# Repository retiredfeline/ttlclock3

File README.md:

# TTL ternary clock

These are the KiCad design files for my Hackaday project [TTL ternary clock](https://hackaday.io/project/183765-ttl-ternary-clock).

Simulations of the 74LS74 based flip-flop-flap and built-up counters are in falstad and logisim directories.

## Versioning

First release January 2022

## Authors

* **Ken Yap**

## License

See the [LICENSE](LICENSE.md) file for license rights and limitations (MIT).

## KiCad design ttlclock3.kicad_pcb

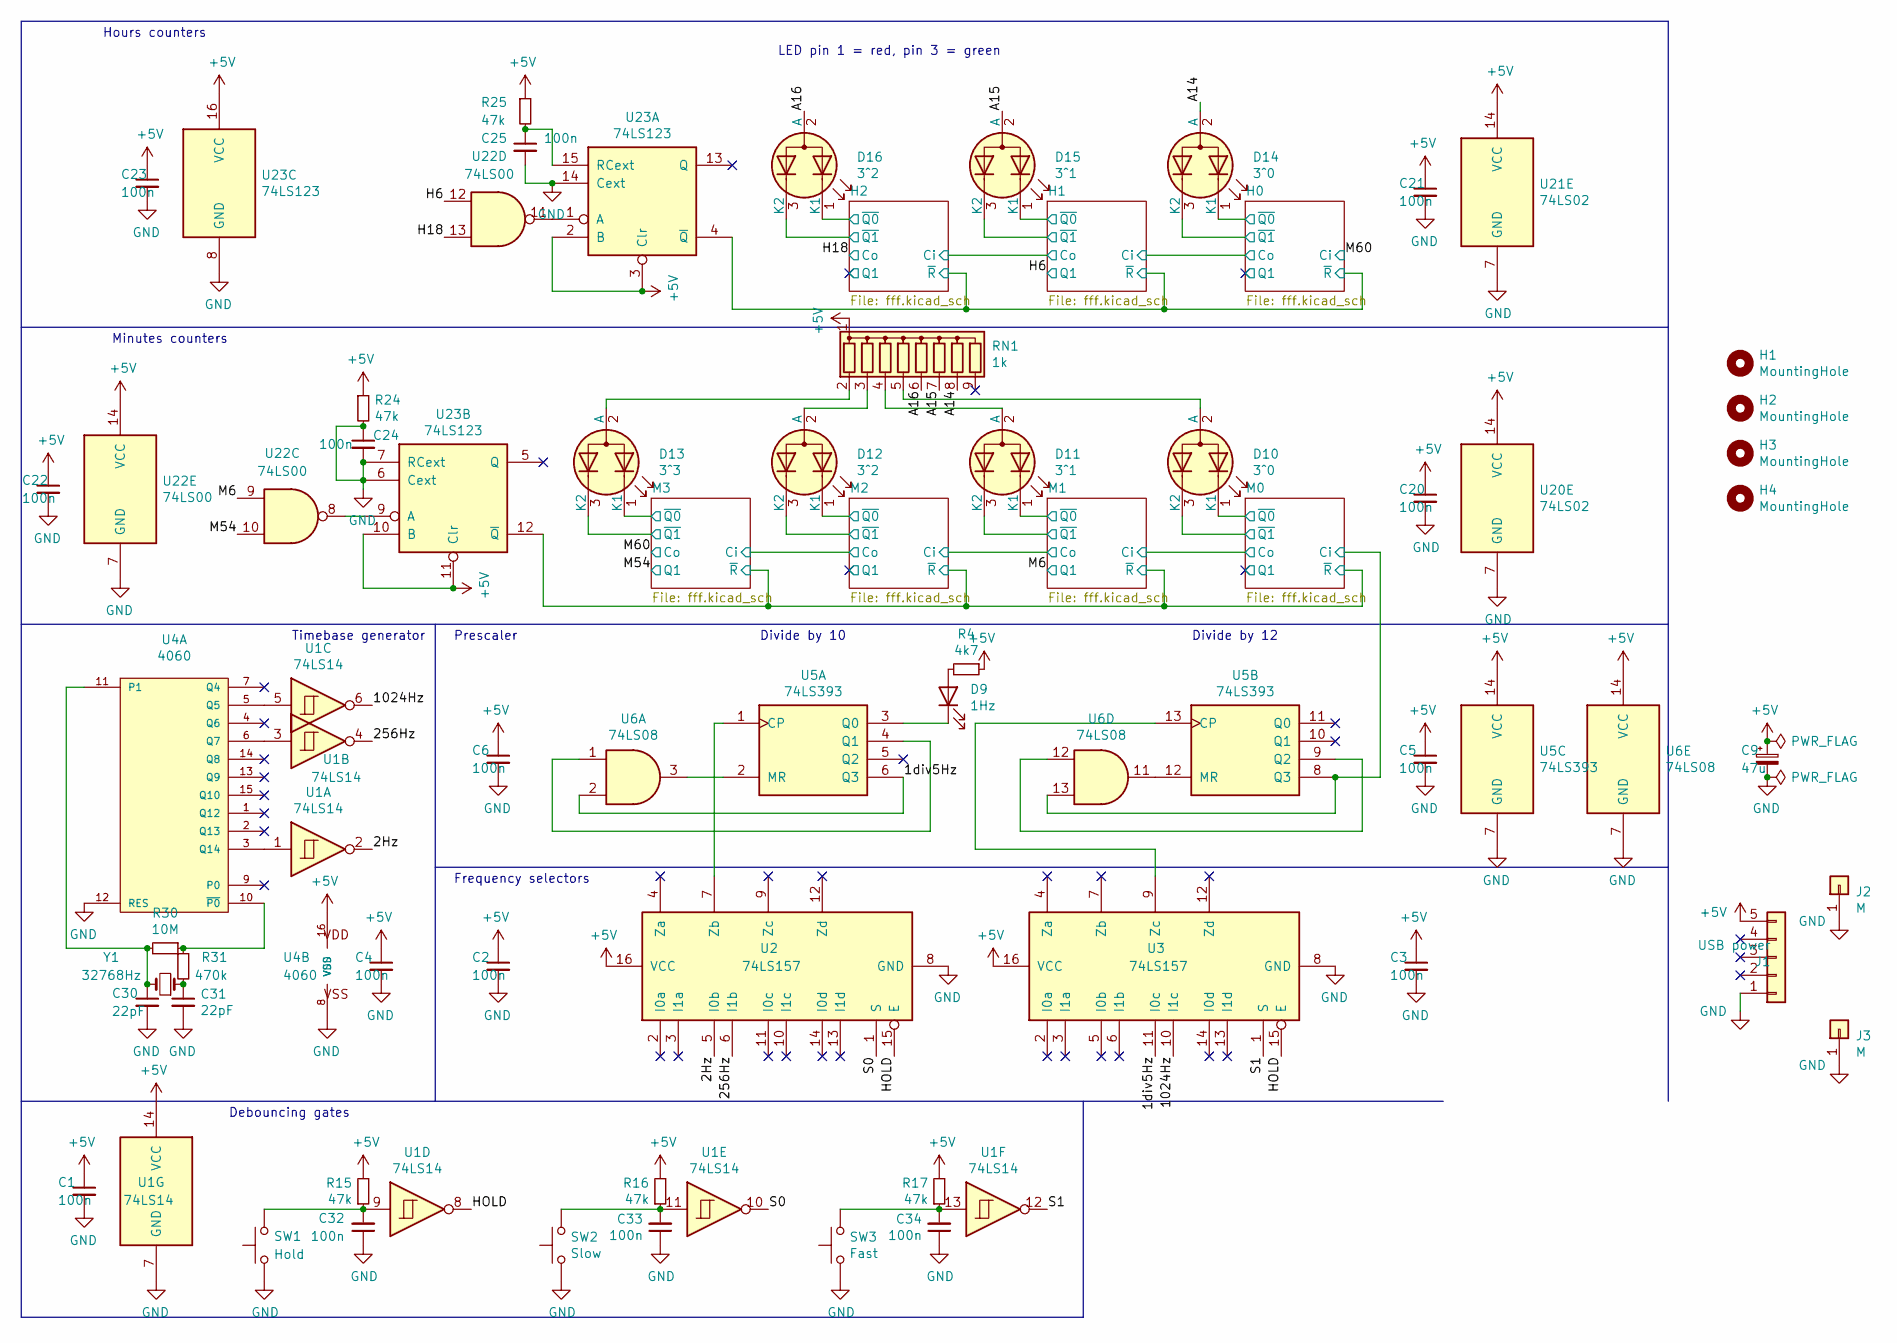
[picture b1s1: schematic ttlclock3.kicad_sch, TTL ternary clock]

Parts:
C1, C2, C3, C4, C5, C6, C20, C21, C22, C23: 100n; C_Rect_L7.2mm_W2.5mm_P5.00mm_FKS2_FKP2_MKS2_MKP2
C9: 47u; CP_Radial_D6.3mm_P2.50mm
C24, C25, C32, C33, C34: 100n; C_Disc_D3.4mm_W2.1mm_P2.50mm
C30, C31: 22pF; C_Disc_D3.0mm_W1.6mm_P2.50mm
D9: 1Hz; LED_D3.0mm
D10, D14: 3^0; LED_D5.0mm-3
D11, D15: 3^1; LED_D5.0mm-3
D12, D16: 3^2; LED_D5.0mm-3
D13: 3^3; LED_D5.0mm-3
H1, H2, H3, H4: MountingHole; MountingHole_3.5mm_Pad
J1: USB power; PinHeader_1x05_P2.54mm_Vertical
J2, J3: M; PinHeader_1x01_P2.54mm_Vertical
R4: 4k7; R_Axial_DIN0207_L6.3mm_D2.5mm_P10.16mm_Horizontal
R15, R16, R17, R24, R25: 47k; R_Axial_DIN0207_L6.3mm_D2.5mm_P10.16mm_Horizontal
R30: 10M; R_Axial_DIN0207_L6.3mm_D2.5mm_P10.16mm_Horizontal
R31: 470k; R_Axial_DIN0207_L6.3mm_D2.5mm_P10.16mm_Horizontal
RN1: 1k; R_Array_SIP9
SW1: Hold; SW_PUSH_6mm_H4.3mm
SW2: Slow; SW_PUSH_6mm_H4.3mm
SW3: Fast; SW_PUSH_6mm_H4.3mm
U1: 74LS14; DIP-14_W7.62mm
U2, U3: 74LS157; DIP-16_W7.62mm
U4: 4060; DIP-16_W7.62mm
U5: 74LS393; DIP-14_W7.62mm
U6: 74LS08; DIP-14_W7.62mm
U20, U21: 74LS02; DIP-14_W7.62mm
U22: 74LS00; DIP-14_W7.62mm
U23: 74LS123; DIP-16_W7.62mm
Y1: 32768Hz; Crystal_C38-LF_D3.0mm_L8.0mm_Horizontal

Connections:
+5V: C1.1, C2.1, C3.1, C4.1, C5.1, C6.1, C9.1, C20.1, C21.1, C22.1, C23.1, J1.5, R4.1, R15.2, R16.2, R17.2, R24.1, R25.1, RN1.1 (common), U1.14 (VCC), U2.16 (VCC), U3.16 (VCC), U4.16 (VDD), U5.14 (VCC), U6.14 (VCC), U20.14 (VCC), U21.14 (VCC), U22.14 (VCC), U23.2 (B), U23.3 (Clr), U23.10 (B), U23.11 (Clr), U23.16 (VCC); also elsewhere on the board
/1div5Hz: U3.11 (I0c), U5.6 (Q3), U6.2
/2Hz: U1.2, U2.5 (I0b)
/256Hz: U1.4, U2.6 (I1b)
/1024Hz: U1.6, U3.10 (I1c)
/A14: D14.2 (A), RN1.8 (R7)
/A15: D15.2 (A), RN1.7 (R6)
/A16: D16.2 (A), RN1.6 (R5)
/H0/~Q0: D14.1 (K1); also elsewhere on the board
/H0/~Q1: D14.3 (K2); also elsewhere on the board
/H0/~R: U23.4 (~Q); also elsewhere on the board
/H1/Co: U21.10; also elsewhere on the board
/H1/~Q0: D15.1 (K1); also elsewhere on the board
/H1/~Q1: D15.3 (K2); also elsewhere on the board
/H2/Q1: U21.3; also elsewhere on the board
/H2/~Q0: D16.1 (K1); also elsewhere on the board
/H2/~Q1: D16.3 (K2); also elsewhere on the board
/H6: U21.9, U22.12; also elsewhere on the board
/H18: U21.1, U22.13; also elsewhere on the board
/HOLD: U1.8, U2.15 (E), U3.15 (E)
/M0/Ci: U5.8 (Q3), U6.13; also elsewhere on the board
/M0/Co: U20.10; also elsewhere on the board
/M0/Q1: U20.9; also elsewhere on the board
/M0/~Q0: D10.1 (K1); also elsewhere on the board
/M0/~Q1: D10.3 (K2); also elsewhere on the board
/M0/~R: U23.12 (~Q); also elsewhere on the board
/M1/~Q0: D11.1 (K1); also elsewhere on the board
/M1/~Q1: D11.3 (K2); also elsewhere on the board
/M2/Co: U20.1; also elsewhere on the board
/M2/Q1: U20.3; also elsewhere on the board
/M2/~Q0: D12.1 (K1); also elsewhere on the board
/M2/~Q1: D12.3 (K2); also elsewhere on the board
/M3/~Q0: D13.1 (K1); also elsewhere on the board
/M3/~Q1: D13.3 (K2); also elsewhere on the board
/M6: U22.9; also elsewhere on the board
/M54: U20.6, U22.10; also elsewhere on the board
/M60: U20.4; also elsewhere on the board
/S0: U1.10, U2.1 (S)
/S1: U1.12, U3.1 (S)
GND: C1.2, C2.2, C3.2, C4.2, C5.2, C6.2, C9.2, C20.2, C21.2, C22.2, C23.2, C24.1, C24.2, C25.2, C30.2, C31.2, C32.1, C33.1, C34.1, J1.1, J2.1, J3.1, R24.2, SW1.1, SW2.1, SW3.1, U1.7 (GND), U2.8 (GND), U3.8 (GND), U4.8 (VSS), U4.12 (RES), U5.7 (GND), U6.7 (GND), U20.7 (GND), U21.7 (GND), U22.7 (GND), U23.6 (Cext), U23.7 (RCext), U23.8 (GND), U23.14 (Cext); also elsewhere on the board
unnamed: C31.1, R31.2, Y1.1
unnamed: C32.2, R15.1, SW1.2, U1.9
unnamed: C33.2, R16.1, SW2.2, U1.11
unnamed: C34.2, R17.1, SW3.2, U1.13
unnamed: D9.2 (A), R4.2
unnamed: D9.1 (K), U5.3 (Q0)
unnamed: D10.2 (A), RN1.5 (R4)
unnamed: D11.2 (A), RN1.4 (R3)
unnamed: D12.2 (A), RN1.3 (R2)
unnamed: D13.2 (A), RN1.2 (R1)
unnamed: U2.7 (Zb), U5.1 (CP)
unnamed: U3.9 (Zc), U5.13 (CP)
unnamed: C30.1, R30.2, U4.11 (P1), Y1.2
unnamed: U1.5, U4.5 (Q5)
unnamed: U1.3, U4.6 (Q7)
unnamed: U1.1, U4.3 (Q14)
unnamed: R30.1, R31.1, U4.10 (~P0)
unnamed: U5.2 (MR), U6.3
unnamed: U5.4 (Q1), U6.1
unnamed: U5.12 (MR), U6.11
unnamed: U5.9 (Q2), U6.12
unnamed 64: U20.8; also elsewhere on the board
unnamed 66: U20.2; also elsewhere on the board
unnamed 67: U20.5; also elsewhere on the board
unnamed 69: U21.8; also elsewhere on the board
unnamed 70: U21.2; also elsewhere on the board
unnamed: U22.11, U23.1 (A)
unnamed: C25.1, R25.2, U23.15 (RCext)
unnamed: U22.8, U23.9 (A)

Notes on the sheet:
Frequency selectors
Divide by 10
Minutes counters
Debouncing gates
LED pin 1 = red, pin 3 = green
Timebase generator
Prescaler
Divide by 12
Hours counters

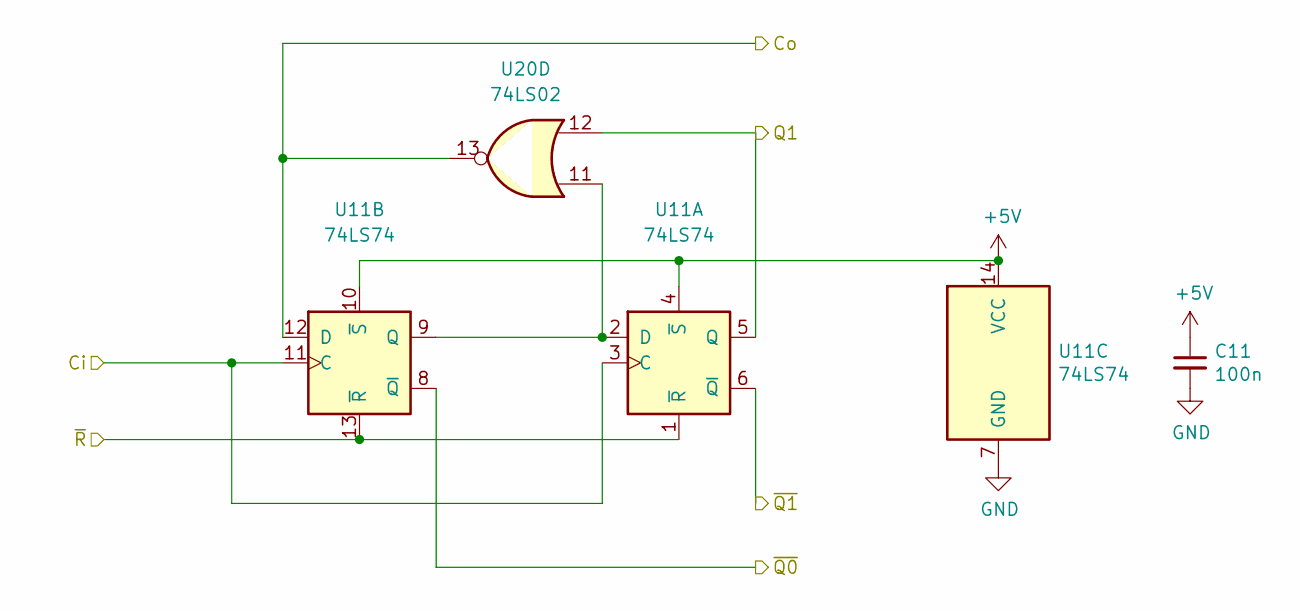
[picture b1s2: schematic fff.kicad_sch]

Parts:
C11: 100n; C_Rect_L7.2mm_W2.5mm_P5.00mm_FKS2_FKP2_MKS2_MKP2
U11: 74LS74; DIP-14_W7.62mm
U20: 74LS02; DIP-14_W7.62mm

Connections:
+5V: C11.1, U11.4 (~S), U11.10 (~S), U11.14 (VCC); also elsewhere on the board
/M0/Co: U11.3 (C), U11.11 (C), U20.10; also elsewhere on the board
/M0/Q1: U20.9; also elsewhere on the board
/M0/~R: U11.1 (~R), U11.13 (~R); also elsewhere on the board
/M1/Co: U11.12 (D), U20.13; also elsewhere on the board
/M1/~Q0: U11.8 (~Q); also elsewhere on the board
/M1/~Q1: U11.6 (~Q); also elsewhere on the board
/M2/Co: U20.1; also elsewhere on the board
/M2/Q1: U20.3; also elsewhere on the board
/M6: U11.5 (Q), U20.12; also elsewhere on the board
/M54: U20.6; also elsewhere on the board
/M60: U20.4; also elsewhere on the board
GND: C11.2, U11.7 (GND); also elsewhere on the board
unnamed 64: U20.8; also elsewhere on the board
unnamed: U11.2 (D), U11.9 (Q), U20.11
unnamed 66: U20.2; also elsewhere on the board
unnamed 67: U20.5; also elsewhere on the board

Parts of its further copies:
C10, C12, C13, C14, C15, C16: 100n; C_Rect_L7.2mm_W2.5mm_P5.00mm_FKS2_FKP2_MKS2_MKP2
U10, U12, U13, U14, U15, U16: 74LS74; DIP-14_W7.62mm

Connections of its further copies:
+5V: C10.1, C12.1, C13.1, C14.1, C15.1, C16.1, U10.4 (~S), U10.10 (~S), U10.14 (VCC), U12.4 (~S), U12.10 (~S), U12.14 (VCC), U13.4 (~S), U13.10 (~S), U13.14 (VCC), U14.4 (~S), U14.10 (~S), U14.14 (VCC), U15.4 (~S), U15.10 (~S), U15.14 (VCC), U16.4 (~S), U16.10 (~S), U16.14 (VCC); also elsewhere on the board
/H0/Co: U14.12 (D), U15.3 (C), U15.11 (C); also elsewhere on the board
/H0/Q1: U14.5 (Q); also elsewhere on the board
/H0/~Q0: U14.8 (~Q); also elsewhere on the board
/H0/~Q1: U14.6 (~Q); also elsewhere on the board
/H0/~R: U14.1 (~R), U14.13 (~R), U15.1 (~R), U15.13 (~R), U16.1 (~R), U16.13 (~R); also elsewhere on the board
/H1/Co: U15.12 (D), U16.3 (C), U16.11 (C); also elsewhere on the board
/H1/~Q0: U15.8 (~Q); also elsewhere on the board
/H1/~Q1: U15.6 (~Q); also elsewhere on the board
/H2/Q1: U16.5 (Q); also elsewhere on the board
/H2/~Q0: U16.8 (~Q); also elsewhere on the board
/H2/~Q1: U16.6 (~Q); also elsewhere on the board
/H6: U15.5 (Q); also elsewhere on the board
/H18: U16.12 (D); also elsewhere on the board
/M0/Ci: U10.3 (C), U10.11 (C); also elsewhere on the board
/M0/Co: U10.12 (D); also elsewhere on the board
/M0/Q1: U10.5 (Q); also elsewhere on the board
/M0/~Q0: U10.8 (~Q); also elsewhere on the board
/M0/~Q1: U10.6 (~Q); also elsewhere on the board
/M0/~R: U10.1 (~R), U10.13 (~R), U12.1 (~R), U12.13 (~R), U13.1 (~R), U13.13 (~R); also elsewhere on the board
/M1/Co: U12.3 (C), U12.11 (C); also elsewhere on the board
/M2/Co: U12.12 (D), U13.3 (C), U13.11 (C); also elsewhere on the board
/M2/Q1: U12.5 (Q); also elsewhere on the board
/M2/~Q0: U12.8 (~Q); also elsewhere on the board
/M2/~Q1: U12.6 (~Q); also elsewhere on the board
/M3/~Q0: U13.8 (~Q); also elsewhere on the board
/M3/~Q1: U13.6 (~Q); also elsewhere on the board
/M54: U13.5 (Q); also elsewhere on the board
/M60: U13.12 (D), U14.3 (C), U14.11 (C); also elsewhere on the board
GND: C10.2, C12.2, C13.2, C14.2, C15.2, C16.2, U10.7 (GND), U12.7 (GND), U13.7 (GND), U14.7 (GND), U15.7 (GND), U16.7 (GND); also elsewhere on the board
unnamed 64: U10.2 (D), U10.9 (Q); also elsewhere on the board
unnamed 66: U12.2 (D), U12.9 (Q); also elsewhere on the board
unnamed 67: U13.2 (D), U13.9 (Q); also elsewhere on the board
unnamed 68: U14.2 (D), U14.9 (Q); also elsewhere on the board
unnamed 69: U15.2 (D), U15.9 (Q); also elsewhere on the board
unnamed 70: U16.2 (D), U16.9 (Q); also elsewhere on the board

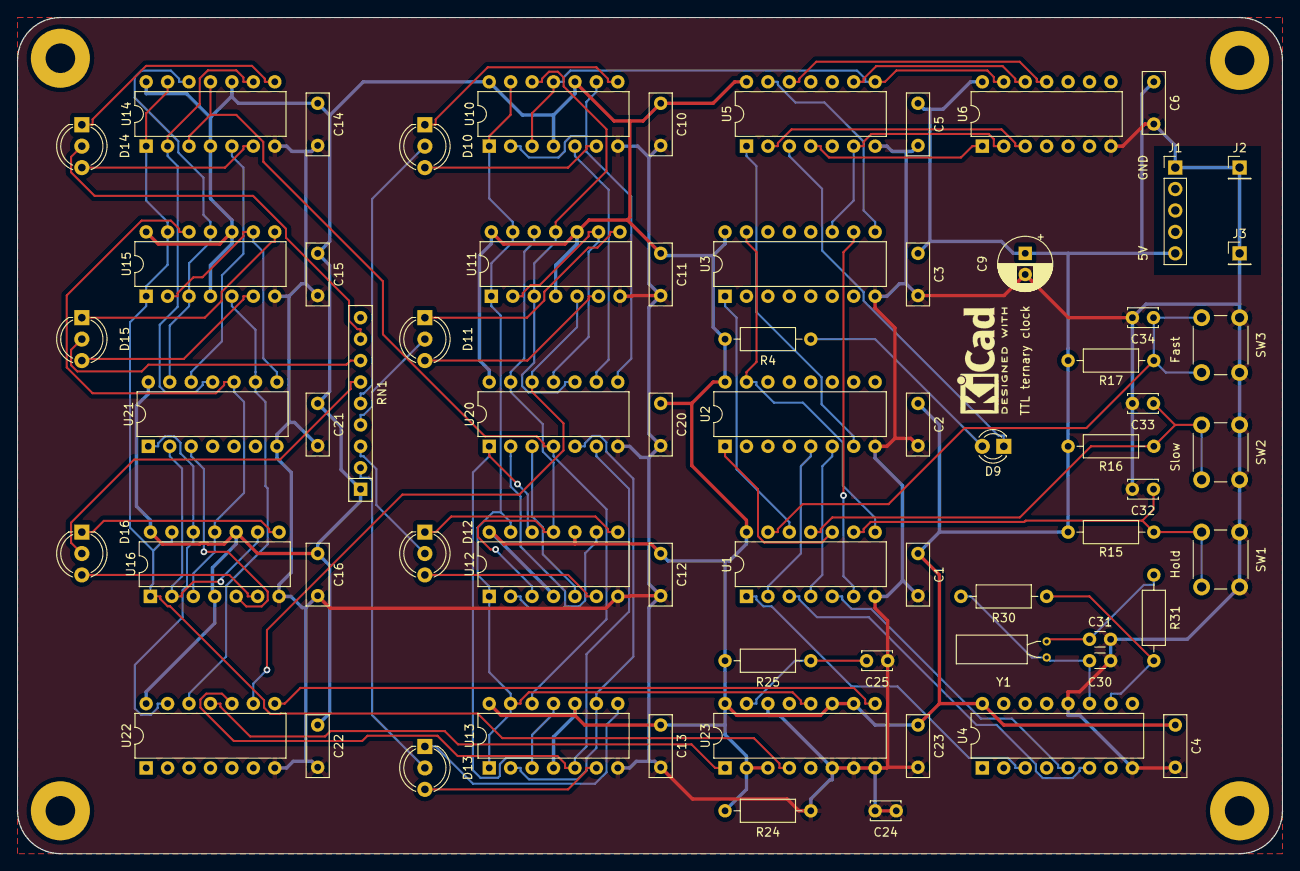
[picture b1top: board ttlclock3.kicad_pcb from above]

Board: 2 copper layers, 149.9 x 99.1 mm, 70 parts (0 on the bottom side), 74 nets.

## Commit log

2021-12-20 First version
2021-12-21 Move flip-flop IC text away from wire
2022-01-26 Add 3D rendering
2022-01-27 Add README.md with link to Hackaday project
2022-01-27 Fix typo
2024-04-02 Update to KiCad 7, not tested
